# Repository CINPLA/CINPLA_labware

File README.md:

# CINPLA_labware

Collection of desigs of PCB and systems used at CINPLA including:

- Encoders: encoders box to measure head-fixed mice running on a wheel
- 2p setup: Arduino-based system for 2-photon setup with visual stimuli, lickport, and reward/aversive delivery through pumps

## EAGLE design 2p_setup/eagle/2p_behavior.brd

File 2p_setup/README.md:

# 2p box

Instructions to build Arduino-based system for 2-photon setup with visual stimuli, lickport, 
and reward/aversive delivery through pumps

It contains the following folders:

- eagle: electronic design with EGALE (.pro - project, .sch - schematics, .brd - board)
- gerber: gerber files for PCB production (the zip file can be sent directly to PCB manufacturers)
- stl: design files to 3D-print the box. 
- arduino: Arduino file (.ino)

For more information, contact Alessio Buccino (alessiop.buccino@gmail.com)

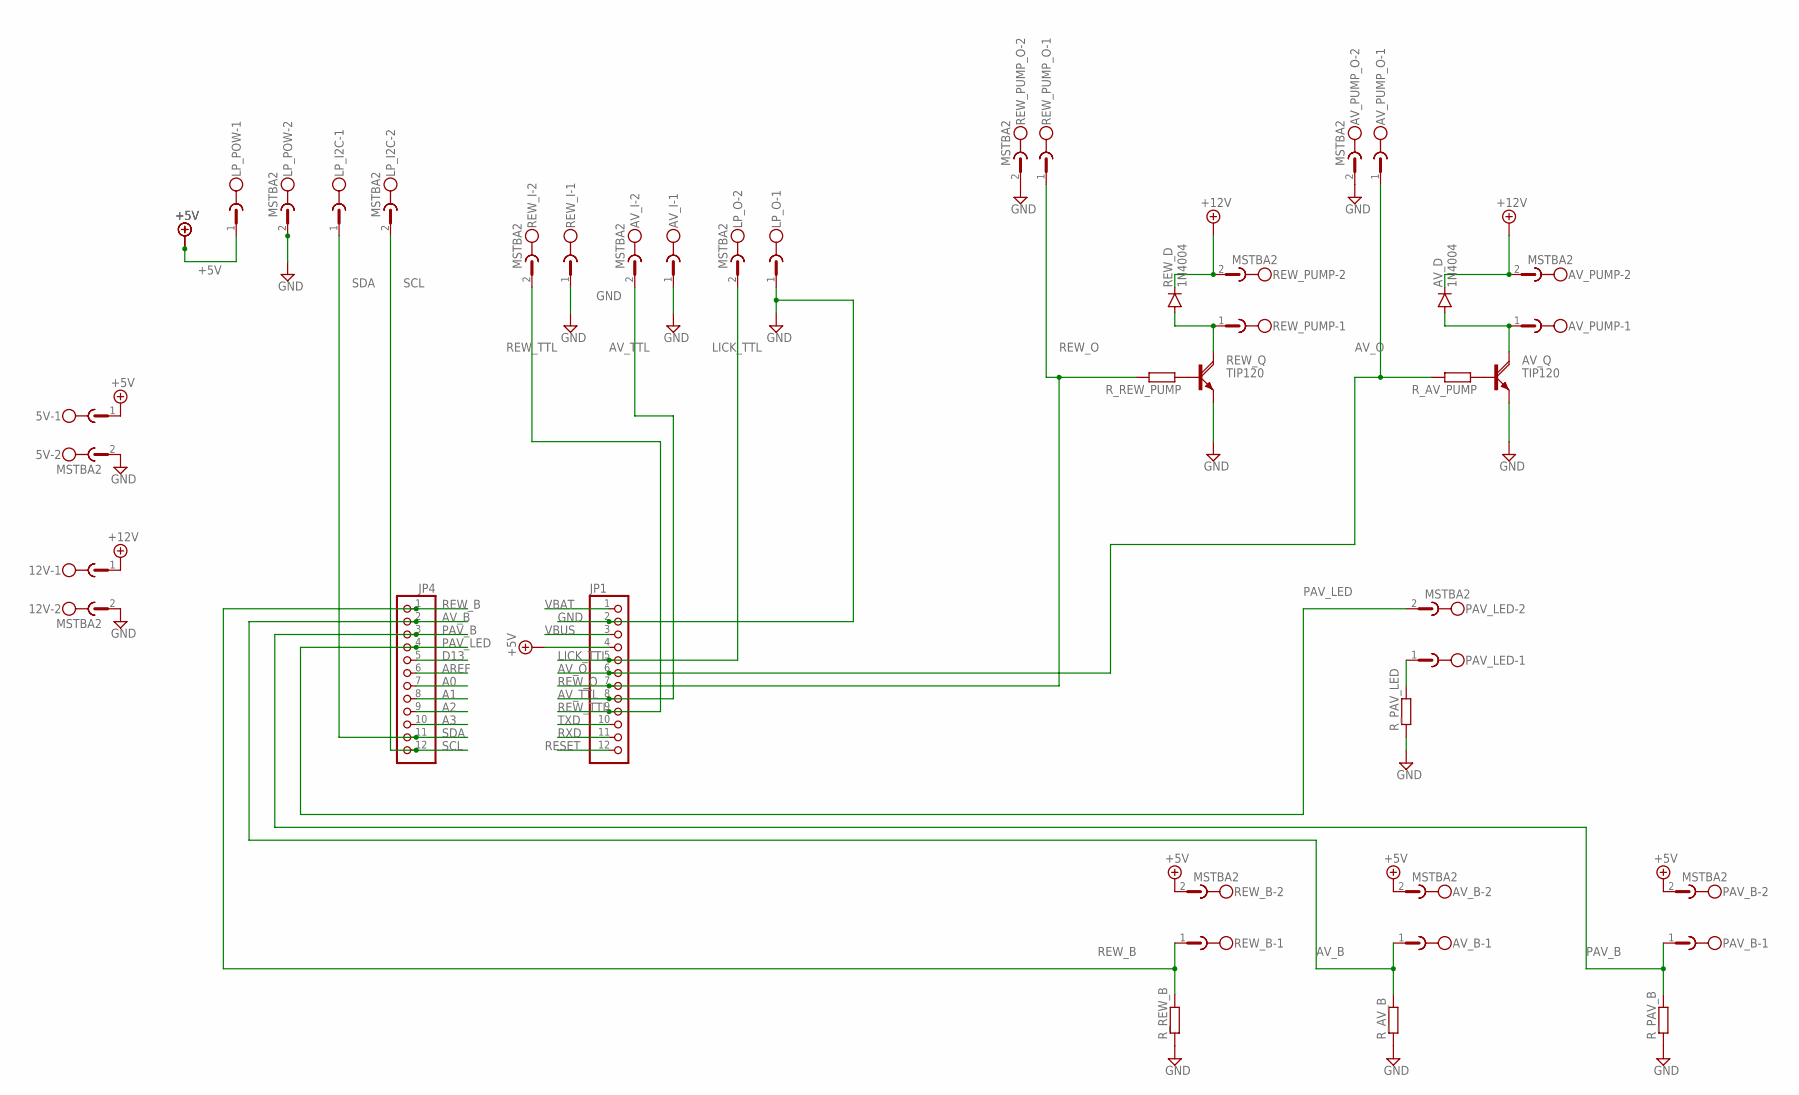
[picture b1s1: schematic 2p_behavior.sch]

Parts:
5V, 12V: MSTBA2
AV_B: MSTBA2
AV_D: 1N4004; DO41-10
AV_I: MSTBA2
AV_PUMP: MSTBA2
AV_PUMP_O: MSTBA2
AV_Q: TIP120; TO220AH
JP1, JP4: PINHD-1X12-CB; 1X12-CB
LP_I2C: MSTBA2
LP_O: MSTBA2
LP_POW: MSTBA2
PAV_B: MSTBA2
PAV_LED: MSTBA2
REW_B: MSTBA2
REW_D: 1N4004; DO41-10
REW_I: MSTBA2
REW_PUMP: MSTBA2
REW_PUMP_O: MSTBA2
REW_Q: TIP120; TO220AH
R_AV_B: R-EU_0207/5V; 0207/5V
R_AV_PUMP: R-EU_0207/5V; 0207/5V
R_PAV_B: R-EU_0207/5V; 0207/5V
R_PAV_LED: R-EU_0207/5V; 0207/5V
R_REW_B: R-EU_0207/5V; 0207/5V
R_REW_PUMP: R-EU_0207/5V; 0207/5V

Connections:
+5V: 5V.1, AV_B.2, JP1.4, LP_POW.1, PAV_B.2, REW_B.2
+12V: 12V.1, AV_D.C, AV_PUMP.2, REW_D.C, REW_PUMP.2
A0: JP4.7
A1: JP4.8
A2: JP4.9
A3: JP4.10
AREF: JP4.6
AV_B: AV_B.1, JP4.2, R_AV_B.2
AV_O: AV_PUMP_O.1, JP1.6, R_AV_PUMP.2
AV_TTL: AV_I.2, JP1.8
D13: JP4.5
GND: 5V.2, 12V.2, AV_I.1, AV_PUMP_O.2, AV_Q.E, JP1.2, LP_O.1, LP_POW.2, REW_I.1, REW_PUMP_O.2, REW_Q.E, R_AV_B.1, R_PAV_B.1, R_PAV_LED.1, R_REW_B.1
LICK_TTL: JP1.5, LP_O.2
unnamed: PAV_LED.1, R_PAV_LED.2
unnamed: REW_Q.B, R_REW_PUMP.1
unnamed: REW_D.A, REW_PUMP.1, REW_Q.C
unnamed: AV_Q.B, R_AV_PUMP.1
unnamed: AV_D.A, AV_PUMP.1, AV_Q.C
PAV_B: JP4.3, PAV_B.1, R_PAV_B.2
PAV_LED: JP4.4, PAV_LED.2
RESET: JP1.12
REW_B: JP4.1, REW_B.1, R_REW_B.2
REW_O: JP1.7, REW_PUMP_O.1, R_REW_PUMP.2
REW_TTL: JP1.9, REW_I.2
RXD: JP1.11
SCL: JP4.12, LP_I2C.2
SDA: JP4.11, LP_I2C.1
TXD: JP1.10
VBAT: JP1.1
VBUS: JP1.3

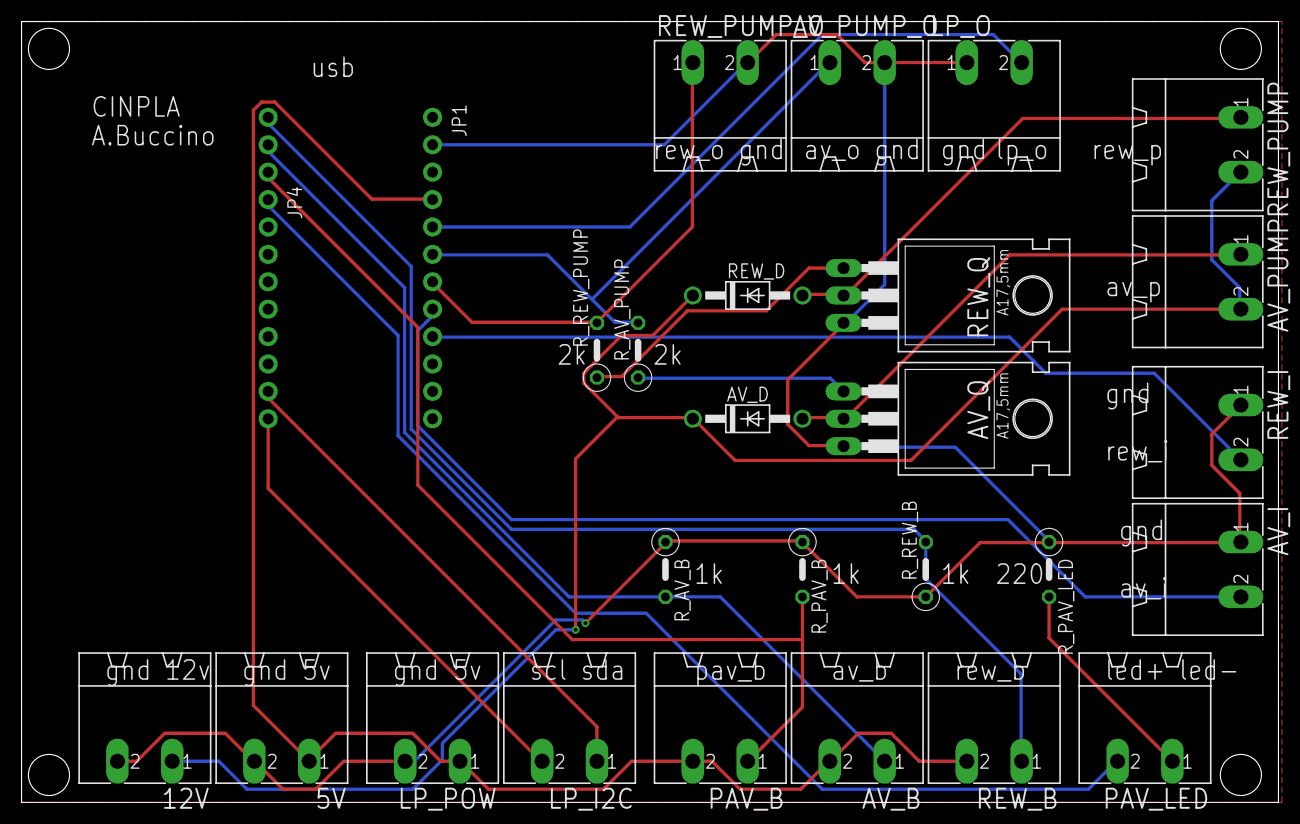
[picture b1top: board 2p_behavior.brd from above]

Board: 2 copper layers, 116.5 x 72.4 mm, 27 parts (0 on the bottom side), 19 nets.

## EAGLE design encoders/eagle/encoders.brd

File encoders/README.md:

# Encoder box

Instructions to build encoder box to measure running speed on treadmill for head-fixed mice.

It contains the following folders:

- eagle: electronic design with EGALE (.pro - project, .sch - schematics, .brd - board)
- gerber: gerber files for PCB production (the zip file can be sent directly to PCB manufacturers)
- stl: design files to 3D-print the box. Two designs are available, one with wire outputs, the other with BCN outputs

For more information, contact Alessio Buccino (alessiop.buccino@gmail.com) or Elise Holter Thompson (e.h.thompson@ibv.uio.no)

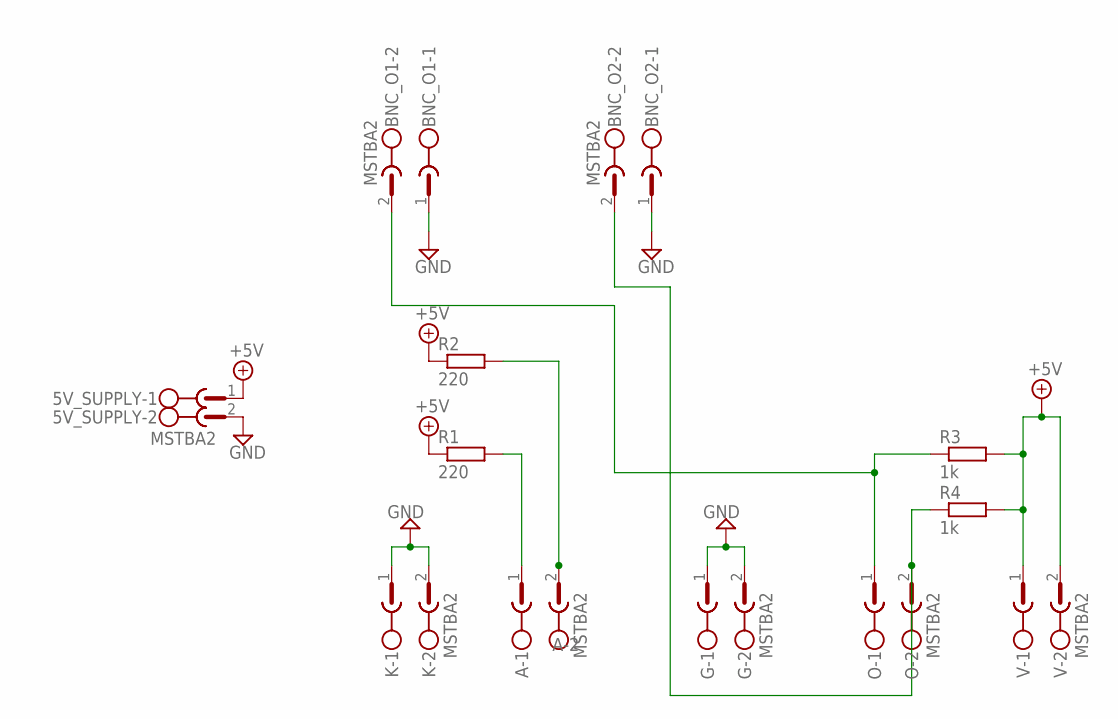
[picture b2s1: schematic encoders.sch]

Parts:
5V_SUPPLY: MSTBA2
A: MSTBA2
BNC_O1, BNC_O2: MSTBA2
G: MSTBA2
K: MSTBA2
O: MSTBA2
R1, R2: 220; 0204/7
R3, R4: 1k; 0204/7
V: MSTBA2

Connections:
+5V: 5V_SUPPLY.1, R1.1, R2.1, R3.2, R4.2, V.1, V.2
GND: 5V_SUPPLY.2, BNC_O1.1, BNC_O2.1, G.1, G.2, K.1, K.2
unnamed: A.1, R1.2
unnamed: A.2, R2.2
unnamed: BNC_O2.2, O.2, R4.1
unnamed: BNC_O1.2, O.1, R3.1

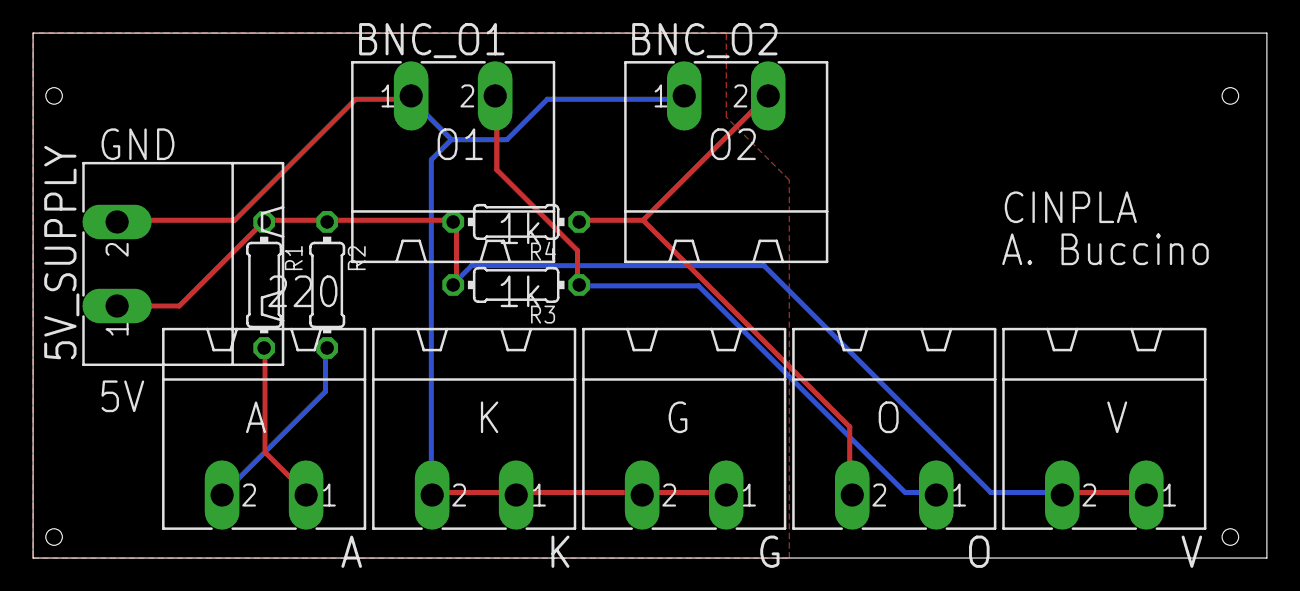
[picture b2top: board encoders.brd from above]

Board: 2 copper layers, 74.6 x 31.7 mm, 12 parts (0 on the bottom side), 6 nets.

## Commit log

2020-02-17 Added files
